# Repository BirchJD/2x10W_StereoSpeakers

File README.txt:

2x10W Stereo Speakers
=====================

See YouTube videos:

3D Printed Stereo Speaker Cases
For Eagle L018A 10W Speakers & STA540 Multiwatt Amplifier
https://www.youtube.com/watch?v=Qkf_tXnQIXA

STA540 Stereo & TDA7266M Mono Bridge Amplifiers Using A Common PCB
https://www.youtube.com/watch?v=eWS_KYsDmyA

The project contains:

Multi Watt Amplifier/   - KiCad Circuit schematic & PCB Gerber files for 2x10W
                          Stereo bridge amplifiers using STA540 amplifier in a
                          MultiWatt package.

                          NOTE: CARE MUST BE TAKEN TO CONNECT THE POWER IN THE
                                CORRECT POLARITY UNLESS A POLARISED CONNECTOR
                                IS USED.

10W75mmCabinet/         - FreeCAD 3D Model Design & STL files for 3D Printing
                          the Eagle L018A 10W speaker cases.

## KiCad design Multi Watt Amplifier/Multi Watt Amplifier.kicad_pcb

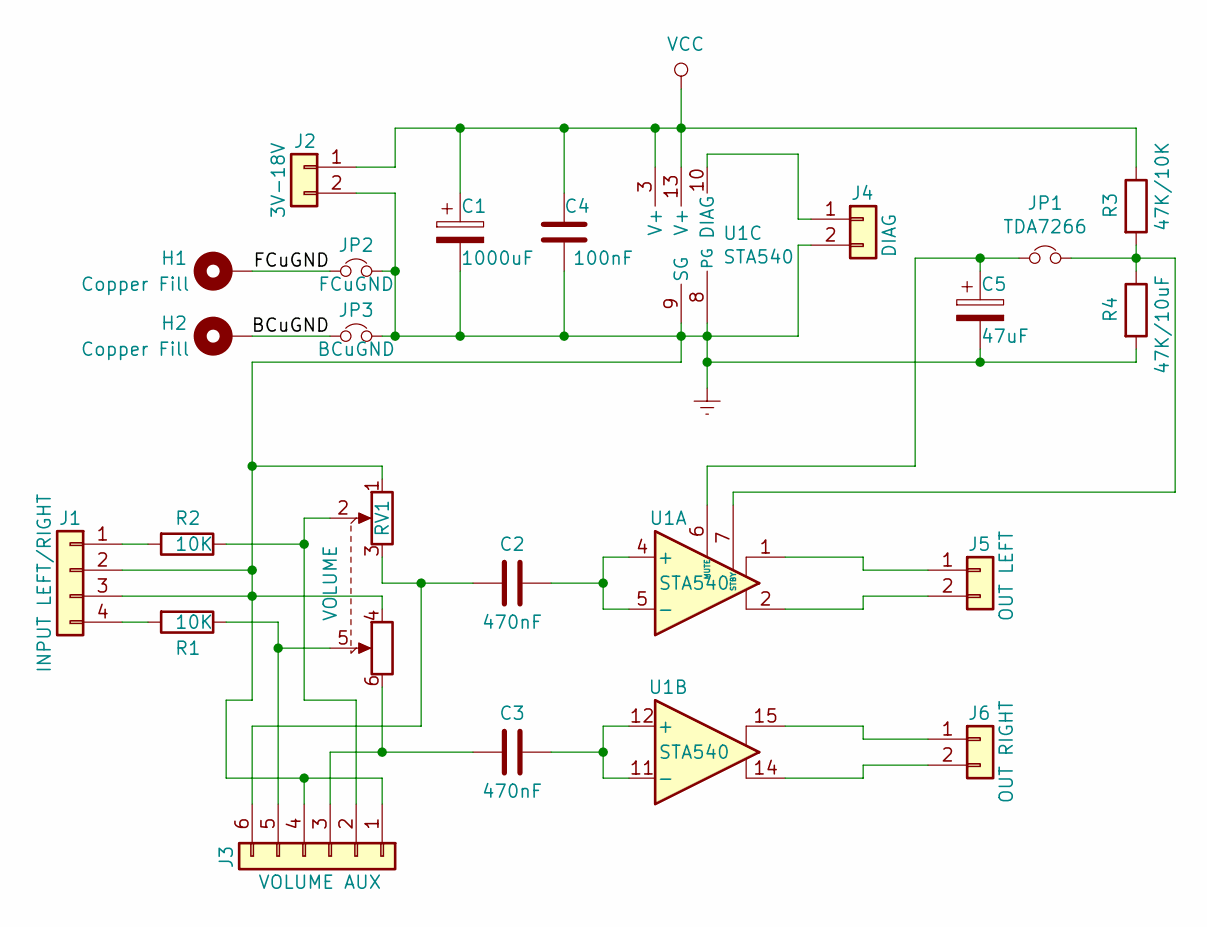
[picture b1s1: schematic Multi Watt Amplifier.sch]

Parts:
C1: 1000uF; CP_Radial_D12.5mm_P5.00mm
C2, C3: 470nF; C_Disc_D5.0mm_W2.5mm_P5.00mm
C4: 100nF; C_Disc_D5.0mm_W2.5mm_P5.00mm
C5: 47uF; CP_Radial_D5.0mm_P2.50mm
H1, H2: Copper Fill; TestPoint_Pad_D2.0mm
J1: INPUT LEFT/RIGHT; PinHeader_1x04_P2.54mm_Vertical
J2: 3V-18V; PinHeader_1x02_P2.54mm_Vertical
J3: VOLUME AUX; PinHeader_1x06_P2.54mm_Vertical
J4: DIAG; PinHeader_1x02_P2.54mm_Vertical
J5: OUT LEFT; PinHeader_1x02_P2.54mm_Vertical
J6: OUT RIGHT; PinHeader_1x02_P2.54mm_Vertical
JP1: TDA7266; SolderJumper-2_P1.3mm_Open_RoundedPad1.0x1.5mm
JP2: FCuGND; SolderJumper-2_P1.3mm_Bridged_RoundedPad1.0x1.5mm
JP3: BCuGND; SolderJumper-2_P1.3mm_Bridged_RoundedPad1.0x1.5mm
R1, R2: 10K; R_Axial_DIN0207_L6.3mm_D2.5mm_P10.16mm_Horizontal
R3: 47K/10K; R_Axial_DIN0207_L6.3mm_D2.5mm_P10.16mm_Horizontal
R4: 47K/10uF; R_Axial_DIN0207_L6.3mm_D2.5mm_P10.16mm_Horizontal
RV1: VOLUME; Potentiometer_Alps_RK163_Dual_Horizontal
U1: STA540; TO-220-15_P2.54x2.54mm_StaggerOdd_Lead4.58mm_Vertical

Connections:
/BCuGND: H2.1, JP3.1
/FCuGND: H1.1, JP2.1
unnamed: C1.2, C4.1, C5.2, J1.2, J1.3, J2.2, J3.1, J3.4, J4.2, JP2.2, JP3.2, R4.2, RV1.1, RV1.4, U1.8 (PG), U1.9 (SG)
unnamed: C2.1, U1.4 (+), U1.5 (-)
unnamed: C2.2, J3.6, RV1.3
unnamed: C3.1, U1.11 (-), U1.12 (+)
unnamed: C3.2, J3.3, RV1.6
unnamed: C5.1, JP1.1, U1.6 (MUTE)
unnamed: J1.1, R2.2
unnamed: J1.4, R1.2
unnamed: J3.2, R2.1, RV1.2
unnamed: J3.5, R1.1, RV1.5
unnamed: J4.1, U1.10 (DIAG)
unnamed: J5.1, U1.1
unnamed: J5.2, U1.2
unnamed: J6.1, U1.15
unnamed: J6.2, U1.14
unnamed: JP1.2, R3.2, R4.1, U1.7 (STBY)
VCC: C1.1, C4.2, J2.1, R3.1, U1.3 (V+), U1.13 (V+)

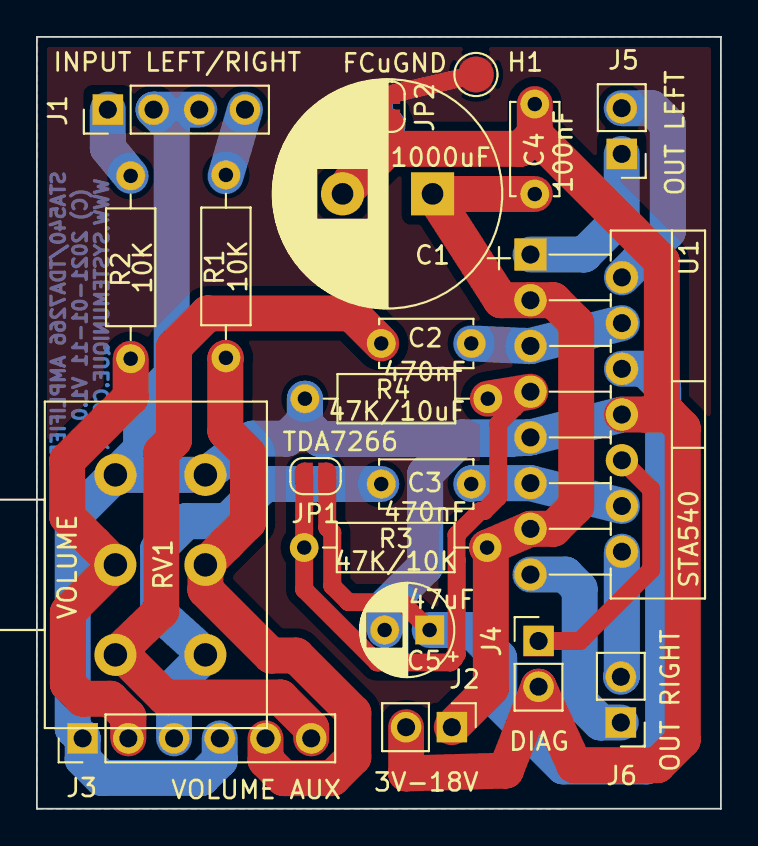
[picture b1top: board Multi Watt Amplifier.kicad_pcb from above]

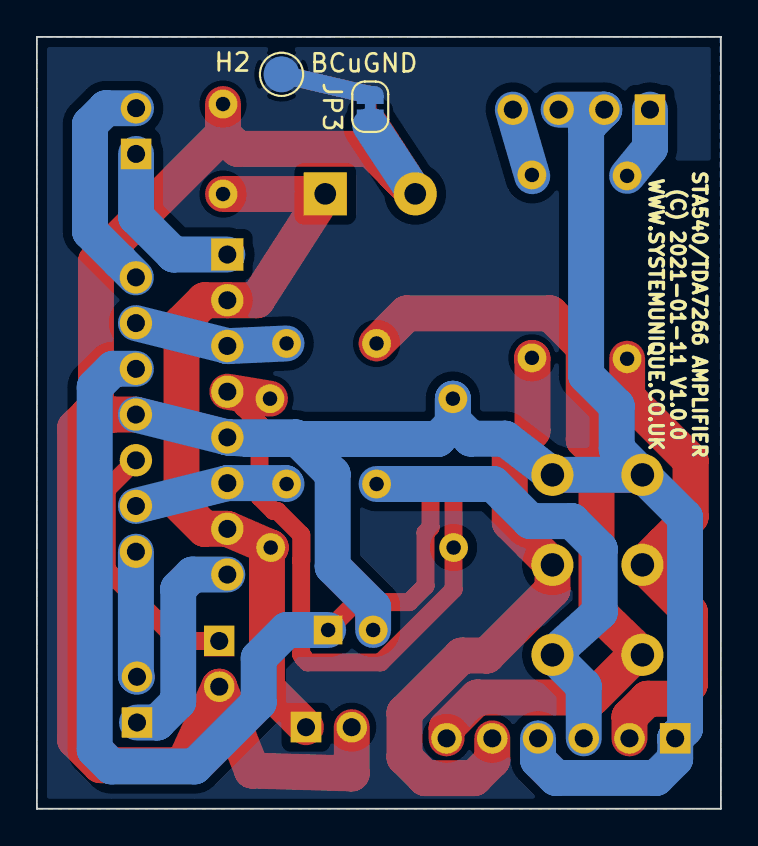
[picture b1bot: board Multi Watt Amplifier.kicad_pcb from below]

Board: 2 copper layers, 38.0 x 42.9 mm, 22 parts (2 on the bottom side), 19 nets.

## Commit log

2021-02-21 Initial commit.

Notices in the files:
Multi Watt Amplifier/Multi Watt Amplifier.kicad_pcb:
(C) 2021-01-11 V1.0.0
